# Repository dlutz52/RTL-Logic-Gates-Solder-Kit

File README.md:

# RTL-Logic-Gates-Solder-Kit
PCB of various logic gates inspired by Ben Eater and implemented as a solder kit. It is a bit over the top in the power supply section, 
but it is my first design as a newbie and was good experience - especially since it took seven versions to get it right...

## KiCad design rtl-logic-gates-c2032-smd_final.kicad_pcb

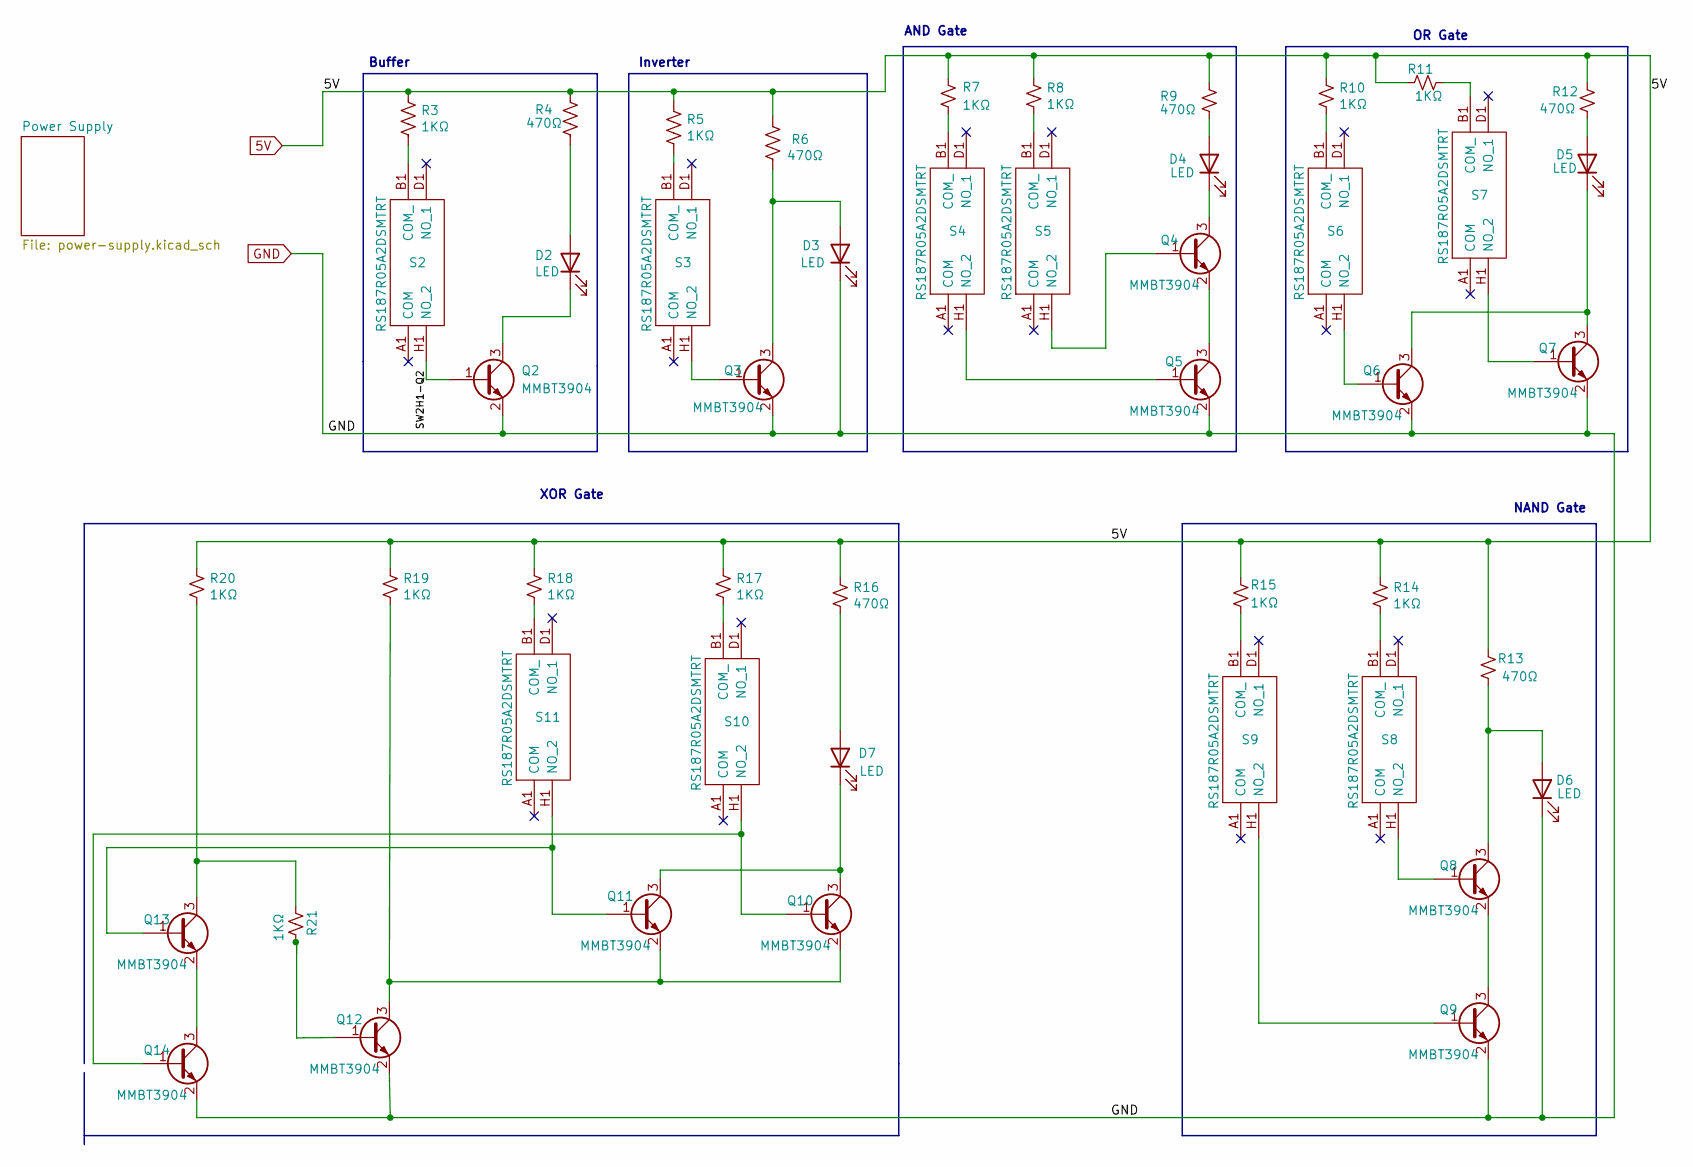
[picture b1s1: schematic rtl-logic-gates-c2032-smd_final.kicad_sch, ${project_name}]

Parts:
D2, D3, D4, D5, D6, D7: LED; LED_1206_3216Metric_Pad1.42x1.75mm_HandSolder
Q2, Q3, Q4, Q5, Q6, Q7, Q8, Q9, Q10, Q11, Q12, Q13, Q14: MMBT3904; SOT-23
R3, R5, R7, R8, R10, R11, R14, R15, R17, R18, R19, R20, R21: 1KΩ; R_1206_3216Metric_Pad1.30x1.75mm_HandSolder
R4, R6, R9, R12, R13, R16: 470Ω; R_1206_3216Metric_Pad1.30x1.75mm_HandSolder
S2, S3, S4, S5, S6, S7, S8, S9, S10, S11: RS187R05A2DSMTRT; Manufacturer_Part_Number RS187R05A2DSMTRT; Mouser Part Number 611-RS187R05A2DSMTRT

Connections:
5V: R3.1, R4.1, R5.1, R6.1, R7.1, R8.1, R9.2, R10.1, R11.1, R12.1, R13.2, R14.1, R15.1, R16.1, R17.1, R18.1, R19.1, R20.1; also elsewhere on the board
/SW2H1-Q2: Q2.1 (B), S2.H1 (NO_2)
GND: D3.1 (K), D6.1 (K), Q2.2 (E), Q3.2 (E), Q5.2 (E), Q6.2 (E), Q7.2 (E), Q9.2 (E), Q12.2 (E), Q14.2 (E); also elsewhere on the board
unnamed: D2.1 (K), Q2.3 (C)
unnamed: D2.2 (A), R4.2
unnamed: D4.1 (K), Q4.3 (C)
unnamed: D4.2 (A), R9.1
unnamed: D5.1 (K), Q6.3 (C), Q7.3 (C)
unnamed: D5.2 (A), R12.2
unnamed: D6.2 (A), Q8.3 (C), R13.1
unnamed: D7.1 (K), Q10.3 (C), Q11.3 (C)
unnamed: D7.2 (A), R16.2
unnamed: Q3.1 (B), S3.H1 (NO_2)
unnamed: D3.2 (A), Q3.3 (C), R6.2
unnamed: Q4.1 (B), S5.H1 (NO_2)
unnamed: Q4.2 (E), Q5.3 (C)
unnamed: Q5.1 (B), S4.H1 (NO_2)
unnamed: Q6.1 (B), S6.H1 (NO_2)
unnamed: Q7.1 (B), S7.H1 (NO_2)
unnamed: Q8.1 (B), S8.H1 (NO_2)
unnamed: Q8.2 (E), Q9.3 (C)
unnamed: Q9.1 (B), S9.H1 (NO_2)
unnamed: Q10.1 (B), Q14.1 (B), S10.H1 (NO_2)
unnamed: Q10.2 (E), Q11.2 (E), Q12.3 (C), R19.2
unnamed: Q11.1 (B), Q13.1 (B), S11.H1 (NO_2)
unnamed: Q12.1 (B), R21.2
unnamed: Q13.2 (E), Q14.3 (C)
unnamed: Q13.3 (C), R20.2, R21.1
unnamed: R3.2, S2.B1 (COM_)
unnamed: R5.2, S3.B1 (COM_)
unnamed: R7.2, S4.B1 (COM_)
unnamed: R8.2, S5.B1 (COM_)
unnamed: R10.2, S6.B1 (COM_)
unnamed: R11.2, S7.B1 (COM_)
unnamed: R14.2, S8.B1 (COM_)
unnamed: R15.2, S9.B1 (COM_)
unnamed: R17.2, S10.B1 (COM_)
unnamed: R18.2, S11.B1 (COM_)

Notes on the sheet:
OR Gate
Inverter
NAND Gate
Buffer
AND Gate
XOR Gate

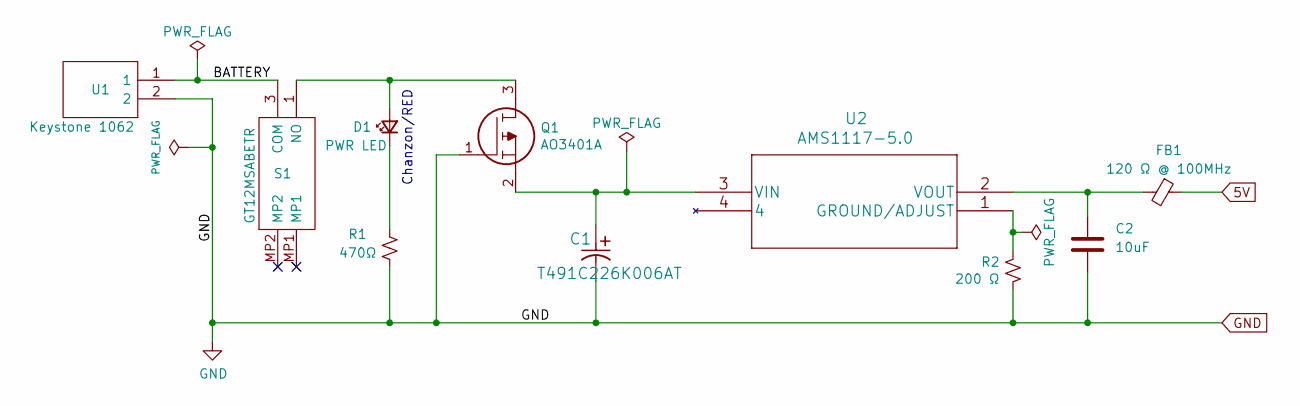
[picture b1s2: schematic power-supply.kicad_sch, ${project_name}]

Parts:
C1: T491C226K006AT; Digikey Part Number 399-3742-1-ND
C2: 10uF; C_1206_3216Metric_Pad1.33x1.80mm_HandSolder
D1: PWR LED; LED_1206_3216Metric_Pad1.42x1.75mm_HandSolder
FB1: 120 Ω @ 100MHz; R_1206_3216Metric_Pad1.30x1.75mm_HandSolder
Q1: AO3401A; SOT95P280X125-3N; Manufacturer_Part_Number AO3401A
R1: 470Ω; R_1206_3216Metric_Pad1.30x1.75mm_HandSolder
R2: 200 Ω; R_1206_3216Metric_Pad1.30x1.75mm_HandSolder
S1: GT12MSABETR; Manufacturer_Part_Number GT12MSABETR; Mouser Part Number 611-GT12MSABETR
U1: Keystone 1062; 1062TR; Manufacturer_Part_Number 1062TR; Mouser Part Number 534-1062TR
U2: AMS1117-5.0

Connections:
5V: FB1.1; also elsewhere on the board
/Power Supply/BATTERY: S1.3 (COM), U1.1
GND: C1.2, C2.2, Q1.1, R1.2, R2.2, U1.2; also elsewhere on the board
unnamed: C1.1, Q1.2, U2.3 (VIN)
unnamed: C2.1, FB1.2, U2.2 (VOUT)
unnamed: D1.1 (K), R1.1
unnamed: D1.2 (A), Q1.3, S1.1 (NO)
unnamed: R2.1, U2.1 (GROUND/ADJUST)

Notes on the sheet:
Chanzon/RED

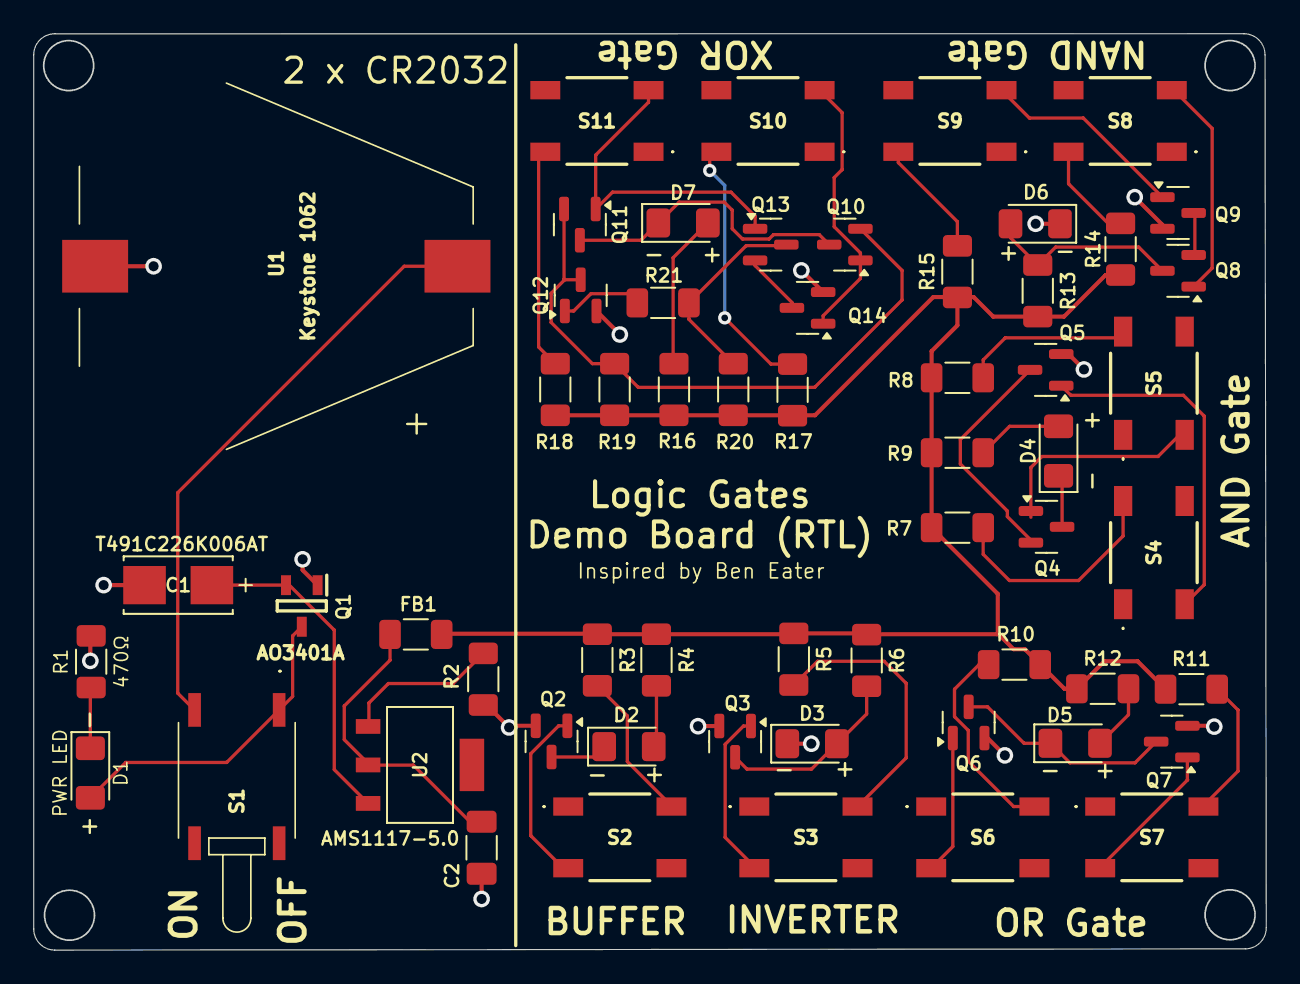
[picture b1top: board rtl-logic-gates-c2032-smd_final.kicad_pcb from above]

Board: 2 copper layers, 74.0 x 55.0 mm, 60 parts (2 on the bottom side), 44 nets.

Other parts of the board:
G1: LOGO; Lutzcraft_logo_1125DPI
REF2: KiCad-Logo2_12mm_SilkScreen

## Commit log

2023-03-02 First and only commit
2023-03-02 Create README.md
    Create README
2023-03-02 Update README.md
    Remove duplication of text.
2024-10-01 Minor edit
2024-10-01 Saved in Kicad v7 and added .gitignore
2024-10-01 Saved in Kicad v8 and added archivew directory to .gitignore
2024-10-01 Saved with Kicad v8 and fixed footprints to clear all DRC errors/warnings
2025-08-17 Upgraded project to KiCad 9.0.3.

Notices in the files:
parts and their libraries:
Copyright 2021 Accelerated Designs. All rights reserved.
